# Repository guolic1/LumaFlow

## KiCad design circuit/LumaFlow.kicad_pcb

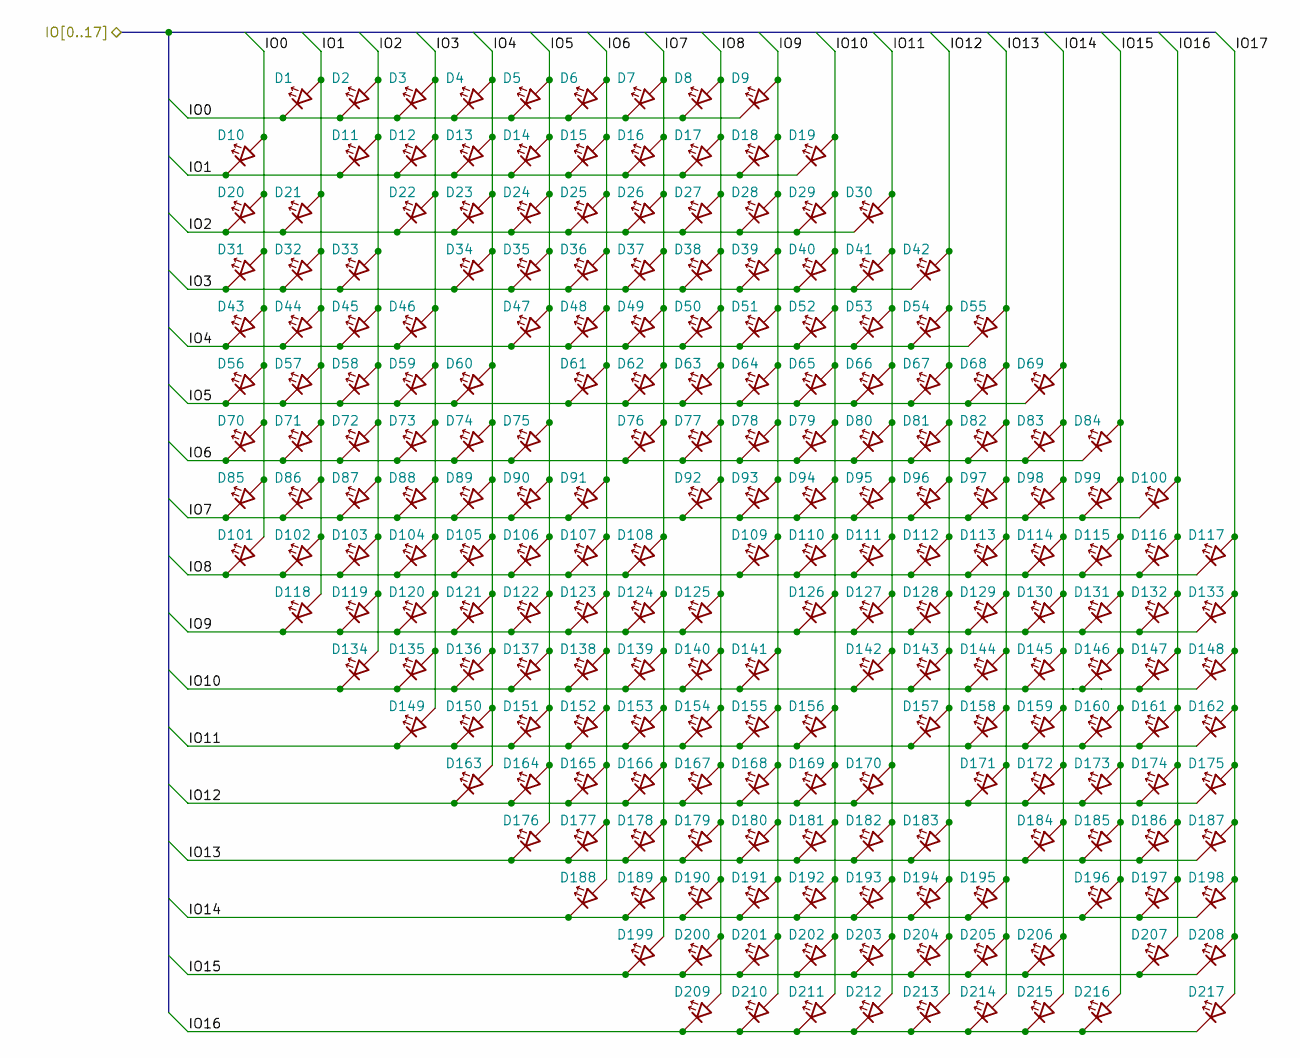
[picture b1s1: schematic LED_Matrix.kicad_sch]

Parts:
D1, D2, D3, D4, D5, D6, D7, D8, D9, D10, D11, D12, D13, D14, D15, D16, D17, D18, D19, D20, D21, D22, D23, D24, D25, D26, D27, D28, D29, D30, D31, D32, D33, D34, D35, D36, D37, D38, D39, D40, D41, D42, D43, D44, D45, D46, D47, D48, D49, D50, D51, D52, D53, D54, D55, D56, D57, D58, D59, D60, D61, D62, D63, D64, D65, D66, D67, D68, D69, D70, D71, D72, D73, D74, D75, D76, D77, D78, D79, D80, D81, D82, D83, D84, D85, D86, D87, D88, D89, D90, D91, D92, D93, D94, D95, D96, D97, D98, D99, D100, D101, D102, D103, D104, D105, D106, D107, D108, D109, D110, D111, D112, D113, D114, D115, D116, D117, D118, D119, D120, D121, D122, D123, D124, D125, D126, D127, D128, D129, D130, D131, D132, D133, D134, D135, D136, D137, D138, D139, D140, D141, D142, D143, D144, D145, D146, D147, D148, D149, D150, D151, D152, D153, D154, D155, D156, D157, D158, D159, D160, D161, D162, D163, D164, D165, D166, D167, D168, D169, D170, D171, D172, D173, D174, D175, D176, D177, D178, D179, D180, D181, D182, D183, D184, D185, D186, D187, D188, D189, D190, D191, D192, D193, D194, D195, D196, D197, D198, D199, D200, D201, D202, D203, D204, D205, D206, D207, D208, D209, D210, D211, D212, D213, D214, D215, D216, D217: LED; LED_0402_1005Metric

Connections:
/LED Matrix/IO0: D1.1 (K), D2.1 (K), D3.1 (K), D4.1 (K), D5.1 (K), D6.1 (K), D7.1 (K), D8.1 (K), D9.1 (K), D10.2 (A), D20.2 (A), D31.2 (A), D43.2 (A), D56.2 (A), D70.2 (A), D85.2 (A), D101.2 (A); also elsewhere on the board
/LED Matrix/IO1: D1.2 (A), D10.1 (K), D11.1 (K), D12.1 (K), D13.1 (K), D14.1 (K), D15.1 (K), D16.1 (K), D17.1 (K), D18.1 (K), D19.1 (K), D21.2 (A), D32.2 (A), D44.2 (A), D57.2 (A), D71.2 (A), D86.2 (A), D102.2 (A), D118.2 (A); also elsewhere on the board
/LED Matrix/IO2: D2.2 (A), D11.2 (A), D20.1 (K), D21.1 (K), D22.1 (K), D23.1 (K), D24.1 (K), D25.1 (K), D26.1 (K), D27.1 (K), D28.1 (K), D29.1 (K), D30.1 (K), D33.2 (A), D45.2 (A), D58.2 (A), D72.2 (A), D87.2 (A), D103.2 (A), D119.2 (A), D134.2 (A); also elsewhere on the board
/LED Matrix/IO3: D3.2 (A), D12.2 (A), D22.2 (A), D31.1 (K), D32.1 (K), D33.1 (K), D34.1 (K), D35.1 (K), D36.1 (K), D37.1 (K), D38.1 (K), D39.1 (K), D40.1 (K), D41.1 (K), D42.1 (K), D46.2 (A), D59.2 (A), D73.2 (A), D88.2 (A), D104.2 (A), D120.2 (A), D135.2 (A), D149.2 (A); also elsewhere on the board
/LED Matrix/IO4: D4.2 (A), D13.2 (A), D23.2 (A), D34.2 (A), D43.1 (K), D44.1 (K), D45.1 (K), D46.1 (K), D47.1 (K), D48.1 (K), D49.1 (K), D50.1 (K), D51.1 (K), D52.1 (K), D53.1 (K), D54.1 (K), D55.1 (K), D60.2 (A), D74.2 (A), D89.2 (A), D105.2 (A), D121.2 (A), D136.2 (A), D150.2 (A), D163.2 (A); also elsewhere on the board
/LED Matrix/IO5: D5.2 (A), D14.2 (A), D24.2 (A), D35.2 (A), D47.2 (A), D56.1 (K), D57.1 (K), D58.1 (K), D59.1 (K), D60.1 (K), D61.1 (K), D62.1 (K), D63.1 (K), D64.1 (K), D65.1 (K), D66.1 (K), D67.1 (K), D68.1 (K), D69.1 (K), D75.2 (A), D90.2 (A), D106.2 (A), D122.2 (A), D137.2 (A), D151.2 (A), D164.2 (A), D176.2 (A); also elsewhere on the board
/LED Matrix/IO6: D6.2 (A), D15.2 (A), D25.2 (A), D36.2 (A), D48.2 (A), D61.2 (A), D70.1 (K), D71.1 (K), D72.1 (K), D73.1 (K), D74.1 (K), D75.1 (K), D76.1 (K), D77.1 (K), D78.1 (K), D79.1 (K), D80.1 (K), D81.1 (K), D82.1 (K), D83.1 (K), D84.1 (K), D91.2 (A), D107.2 (A), D123.2 (A), D138.2 (A), D152.2 (A), D165.2 (A), D177.2 (A), D188.2 (A); also elsewhere on the board
/LED Matrix/IO7: D7.2 (A), D16.2 (A), D26.2 (A), D37.2 (A), D49.2 (A), D62.2 (A), D76.2 (A), D85.1 (K), D86.1 (K), D87.1 (K), D88.1 (K), D89.1 (K), D90.1 (K), D91.1 (K), D92.1 (K), D93.1 (K), D94.1 (K), D95.1 (K), D96.1 (K), D97.1 (K), D98.1 (K), D99.1 (K), D100.1 (K), D108.2 (A), D124.2 (A), D139.2 (A), D153.2 (A), D166.2 (A), D178.2 (A), D189.2 (A), D199.2 (A); also elsewhere on the board
/LED Matrix/IO8: D8.2 (A), D17.2 (A), D27.2 (A), D38.2 (A), D50.2 (A), D63.2 (A), D77.2 (A), D92.2 (A), D101.1 (K), D102.1 (K), D103.1 (K), D104.1 (K), D105.1 (K), D106.1 (K), D107.1 (K), D108.1 (K), D109.1 (K), D110.1 (K), D111.1 (K), D112.1 (K), D113.1 (K), D114.1 (K), D115.1 (K), D116.1 (K), D117.1 (K), D125.2 (A), D140.2 (A), D154.2 (A), D167.2 (A), D179.2 (A), D190.2 (A), D200.2 (A), D209.2 (A); also elsewhere on the board
/LED Matrix/IO9: D9.2 (A), D18.2 (A), D28.2 (A), D39.2 (A), D51.2 (A), D64.2 (A), D78.2 (A), D93.2 (A), D109.2 (A), D118.1 (K), D119.1 (K), D120.1 (K), D121.1 (K), D122.1 (K), D123.1 (K), D124.1 (K), D125.1 (K), D126.1 (K), D127.1 (K), D128.1 (K), D129.1 (K), D130.1 (K), D131.1 (K), D132.1 (K), D133.1 (K), D141.2 (A), D155.2 (A), D168.2 (A), D180.2 (A), D191.2 (A), D201.2 (A), D210.2 (A); also elsewhere on the board
/LED Matrix/IO10: D19.2 (A), D29.2 (A), D40.2 (A), D52.2 (A), D65.2 (A), D79.2 (A), D94.2 (A), D110.2 (A), D126.2 (A), D134.1 (K), D135.1 (K), D136.1 (K), D137.1 (K), D138.1 (K), D139.1 (K), D140.1 (K), D141.1 (K), D142.1 (K), D143.1 (K), D144.1 (K), D145.1 (K), D146.1 (K), D147.1 (K), D148.1 (K), D156.2 (A), D169.2 (A), D181.2 (A), D192.2 (A), D202.2 (A), D211.2 (A); also elsewhere on the board
/LED Matrix/IO11: D30.2 (A), D41.2 (A), D53.2 (A), D66.2 (A), D80.2 (A), D95.2 (A), D111.2 (A), D127.2 (A), D142.2 (A), D149.1 (K), D150.1 (K), D151.1 (K), D152.1 (K), D153.1 (K), D154.1 (K), D155.1 (K), D156.1 (K), D157.1 (K), D158.1 (K), D159.1 (K), D160.1 (K), D161.1 (K), D162.1 (K), D170.2 (A), D182.2 (A), D193.2 (A), D203.2 (A), D212.2 (A); also elsewhere on the board
/LED Matrix/IO12: D42.2 (A), D54.2 (A), D67.2 (A), D81.2 (A), D96.2 (A), D112.2 (A), D128.2 (A), D143.2 (A), D157.2 (A), D163.1 (K), D164.1 (K), D165.1 (K), D166.1 (K), D167.1 (K), D168.1 (K), D169.1 (K), D170.1 (K), D171.1 (K), D172.1 (K), D173.1 (K), D174.1 (K), D175.1 (K), D183.2 (A), D194.2 (A), D204.2 (A), D213.2 (A); also elsewhere on the board
/LED Matrix/IO13: D55.2 (A), D68.2 (A), D82.2 (A), D97.2 (A), D113.2 (A), D129.2 (A), D144.2 (A), D158.2 (A), D171.2 (A), D176.1 (K), D177.1 (K), D178.1 (K), D179.1 (K), D180.1 (K), D181.1 (K), D182.1 (K), D183.1 (K), D184.1 (K), D185.1 (K), D186.1 (K), D187.1 (K), D195.2 (A), D205.2 (A), D214.2 (A); also elsewhere on the board
/LED Matrix/IO14: D69.2 (A), D83.2 (A), D98.2 (A), D114.2 (A), D130.2 (A), D145.2 (A), D159.2 (A), D172.2 (A), D184.2 (A), D188.1 (K), D189.1 (K), D190.1 (K), D191.1 (K), D192.1 (K), D193.1 (K), D194.1 (K), D195.1 (K), D196.1 (K), D197.1 (K), D198.1 (K), D206.2 (A), D215.2 (A); also elsewhere on the board
/LED Matrix/IO15: D84.2 (A), D99.2 (A), D115.2 (A), D131.2 (A), D146.2 (A), D160.2 (A), D173.2 (A), D185.2 (A), D196.2 (A), D199.1 (K), D200.1 (K), D201.1 (K), D202.1 (K), D203.1 (K), D204.1 (K), D205.1 (K), D206.1 (K), D207.1 (K), D208.1 (K), D216.2 (A); also elsewhere on the board
/LED Matrix/IO16: D100.2 (A), D116.2 (A), D132.2 (A), D147.2 (A), D161.2 (A), D174.2 (A), D186.2 (A), D197.2 (A), D207.2 (A), D209.1 (K), D210.1 (K), D211.1 (K), D212.1 (K), D213.1 (K), D214.1 (K), D215.1 (K), D216.1 (K), D217.1 (K); also elsewhere on the board
/LED Matrix/IO17: D117.2 (A), D133.2 (A), D148.2 (A), D162.2 (A), D175.2 (A), D187.2 (A), D198.2 (A), D208.2 (A), D217.2 (A); also elsewhere on the board

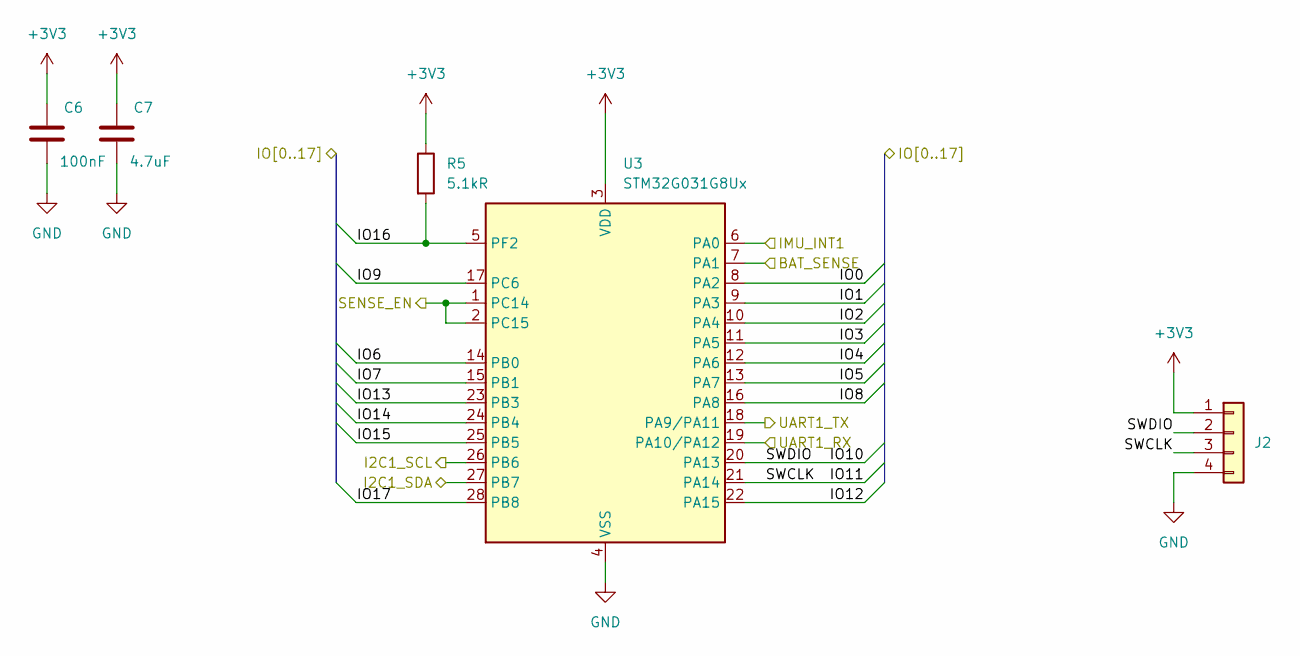
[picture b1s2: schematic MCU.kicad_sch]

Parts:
C6: 100nF; C_0402_1005Metric
C7: 4.7uF; C_0402_1005Metric
J2: Conn_01x04; PinSocket_1x04_P1.27mm_Vertical
R5: 5.1kR; R_0402_1005Metric
U3: STM32G031G8Ux; QFN-28_4x4mm_P0.5mm

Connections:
+3V3: C6.1, C7.1, J2.1, R5.1, U3.3 (VDD); also elsewhere on the board
/IMU/INT1: U3.6 (PA0); also elsewhere on the board
/IMU/SCL: U3.26 (PB6); also elsewhere on the board
/IMU/SDA: U3.27 (PB7); also elsewhere on the board
/LED Matrix/IO0: U3.8 (PA2); also elsewhere on the board
/LED Matrix/IO1: U3.9 (PA3); also elsewhere on the board
/LED Matrix/IO2: U3.10 (PA4); also elsewhere on the board
/LED Matrix/IO3: U3.11 (PA5); also elsewhere on the board
/LED Matrix/IO4: U3.12 (PA6); also elsewhere on the board
/LED Matrix/IO5: U3.13 (PA7); also elsewhere on the board
/LED Matrix/IO6: U3.14 (PB0); also elsewhere on the board
/LED Matrix/IO7: U3.15 (PB1); also elsewhere on the board
/LED Matrix/IO8: U3.16 (PA8); also elsewhere on the board
/LED Matrix/IO9: U3.17 (PC6); also elsewhere on the board
/LED Matrix/IO10: J2.2, U3.20 (PA13); also elsewhere on the board
/LED Matrix/IO11: J2.3, U3.21 (PA14); also elsewhere on the board
/LED Matrix/IO12: U3.22 (PA15); also elsewhere on the board
/LED Matrix/IO13: U3.23 (PB3); also elsewhere on the board
/LED Matrix/IO14: U3.24 (PB4); also elsewhere on the board
/LED Matrix/IO15: U3.25 (PB5); also elsewhere on the board
/LED Matrix/IO16: R5.2, U3.5 (PF2); also elsewhere on the board
/LED Matrix/IO17: U3.28 (PB8); also elsewhere on the board
/MCU/BAT_SENSE: U3.7 (PA1); also elsewhere on the board
/MCU/SENSE_EN: U3.1 (PC14), U3.2 (PC15); also elsewhere on the board
/MCU/UART1_RX: U3.19 (PA10/PA12); also elsewhere on the board
/MCU/UART1_TX: U3.18 (PA9/PA11); also elsewhere on the board
GND: C6.2, C7.2, J2.4, U3.4 (VSS); also elsewhere on the board

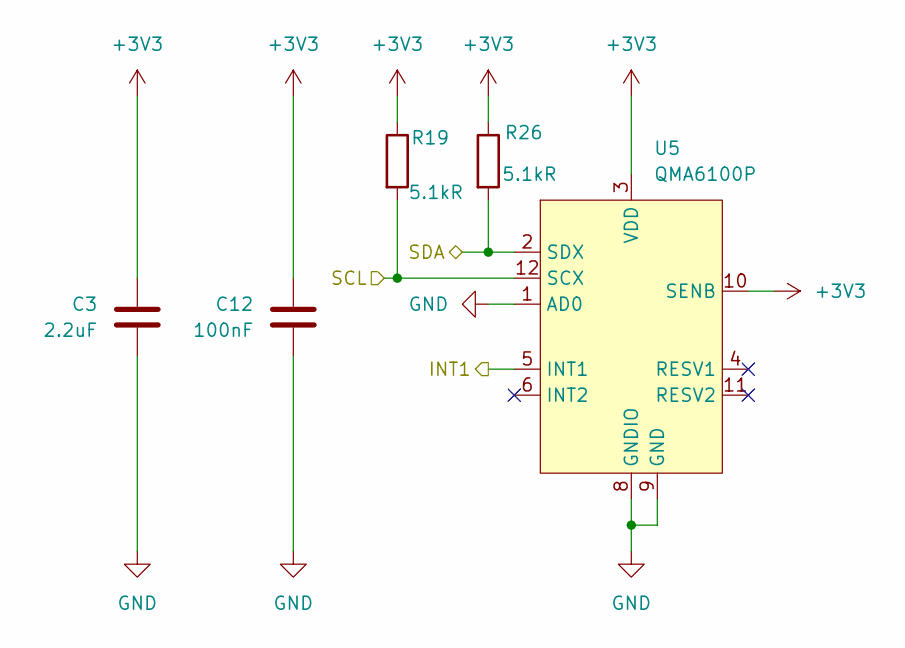
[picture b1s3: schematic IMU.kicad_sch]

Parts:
C3: 2.2uF; C_0402_1005Metric
C12: 100nF; C_0402_1005Metric
R19, R26: 5.1kR; R_0402_1005Metric
U5: QMA6100P; LGA-12_2x2mm_P0.5mm

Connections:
+3V3: C3.1, C12.1, R19.1, R26.1, U5.3 (VDD), U5.10 (SENB); also elsewhere on the board
/IMU/INT1: U5.5 (INT1); also elsewhere on the board
/IMU/SCL: R19.2, U5.12 (SCX); also elsewhere on the board
/IMU/SDA: R26.2, U5.2 (SDX); also elsewhere on the board
GND: C3.2, C12.2, U5.1 (AD0), U5.8 (GNDIO), U5.9 (GND); also elsewhere on the board

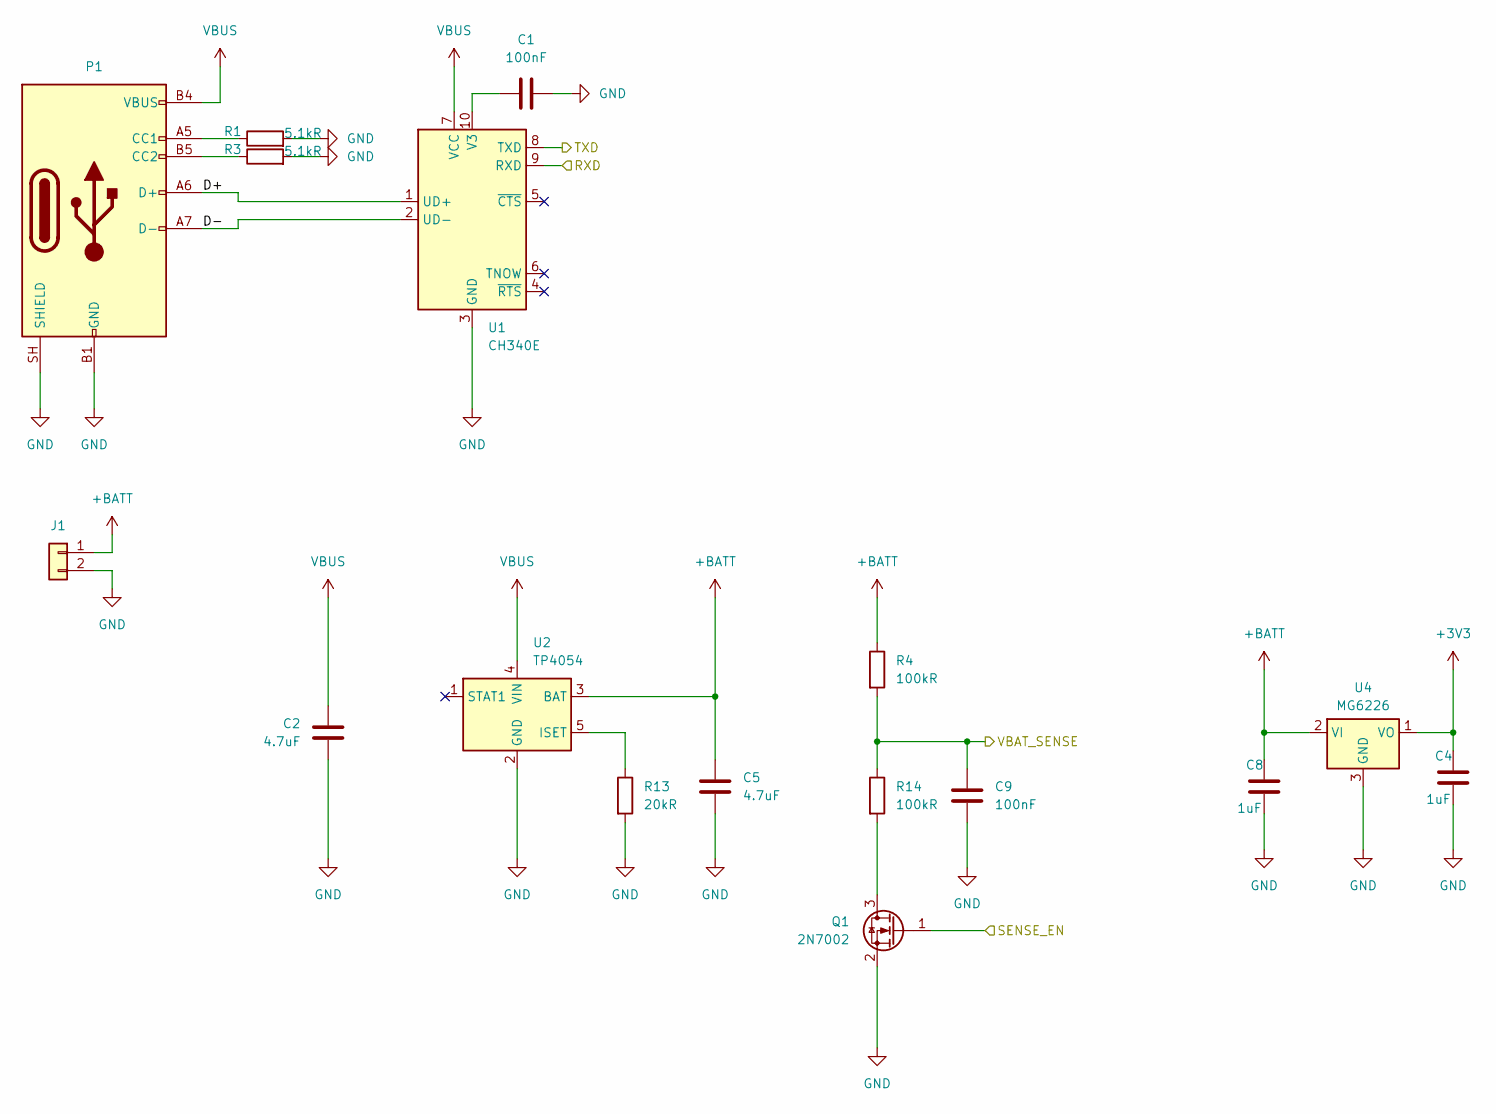
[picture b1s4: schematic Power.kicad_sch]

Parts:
C1, C9: 100nF; C_0402_1005Metric
C2, C5: 4.7uF; C_0402_1005Metric
C4, C8: 1uF; C_0402_1005Metric
J1: Conn_01x02
P1: USB_C_Plug_USB2.0_8Pin; USB-C-SMD_MC-402L68
Q1: 2N7002; SOT-323_SC-70
R1, R3: 5.1kR; R_0402_1005Metric
R4, R14: 100kR; R_0402_1005Metric
R13: 20kR; R_0402_1005Metric
U1: CH340E; MSOP-10_3x3mm_P0.5mm
U2: TP4054; SOT-23-5
U4: MG6226; SOT-23-3

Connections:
+3V3: C4.1, U4.1 (VO); also elsewhere on the board
+BATT: C5.1, C8.1, J1.1, R4.1, U2.3 (BAT), U4.2 (VI)
/MCU/BAT_SENSE: C9.1, R4.2, R14.1; also elsewhere on the board
/MCU/SENSE_EN: Q1.1 (G); also elsewhere on the board
/MCU/UART1_RX: U1.8 (TXD); also elsewhere on the board
/MCU/UART1_TX: U1.9 (RXD); also elsewhere on the board
/Power/D+: P1.A6 (D+), U1.1 (UD+)
/Power/D-: P1.A7 (D-), U1.2 (UD-)
GND: C1.2, C2.2, C4.2, C5.2, C8.2, C9.2, J1.2, P1.B1 (GND), P1.B12 (GND), P1.SH (SHIELD), Q1.2 (S), R1.2, R3.2, R13.2, U1.3 (GND), U2.2 (GND), U4.3 (GND); also elsewhere on the board
unnamed: P1.A5 (CC1), R1.1
unnamed: P1.B5 (CC2), R3.1
unnamed: Q1.3 (D), R14.2
unnamed: C1.1, U1.10 (V3)
unnamed: R13.1, U2.5 (ISET)
VBUS: C2.1, P1.B4 (VBUS), P1.B9 (VBUS), U1.7 (VCC), U2.4 (VIN)

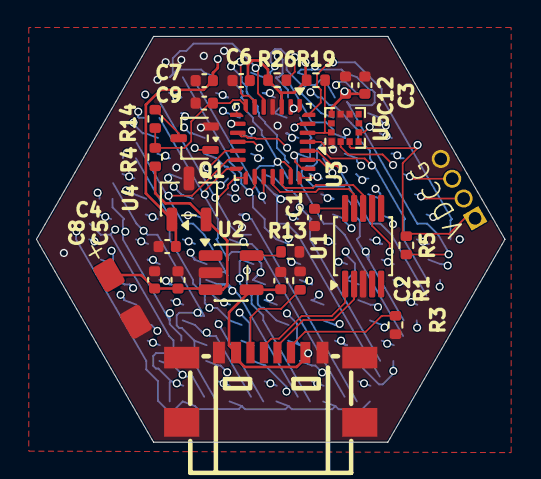
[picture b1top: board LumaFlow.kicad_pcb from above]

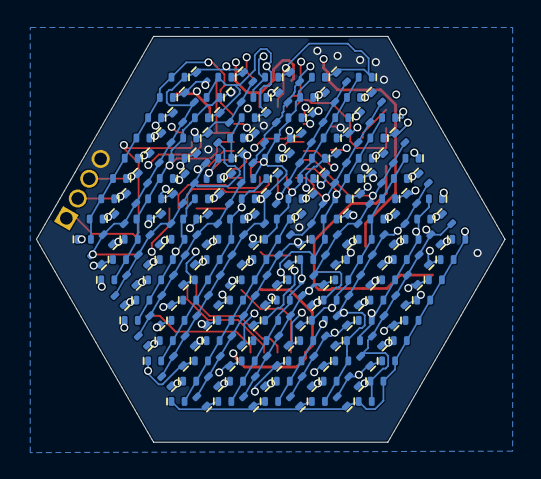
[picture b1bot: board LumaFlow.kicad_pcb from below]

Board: 4 copper layers, 26.0 x 22.5 mm, 244 parts (217 on the bottom side), 36 nets.

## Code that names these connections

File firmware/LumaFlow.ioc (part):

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Mcu.Name=STM32G031G(4-6-8)Ux
Mcu.Package=UFQFPN28
Mcu.UserName=STM32G031G8Ux
PA0.GPIOParameters=GPIO_Label
PA0.GPIO_Label=IMU_INT
PA0.Signal=GPXTI0
PA1.GPIOParameters=GPIO_Label
PA1.GPIO_Label=BAT_SENSE
PA1.Mode=IN1
PA1.Signal=ADC1_IN1
PA10\ [PA12].Mode=Asynchronous
PA10\ [PA12].Signal=USART1_RX
PA13.GPIOParameters=GPIO_Label
PA13.GPIO_Label=IO10
PA13.Mode=Serial_Wire
PA13.Signal=SYS_SWDIO
PA14-BOOT0.GPIOParameters=GPIO_Label
PA14-BOOT0.GPIO_Label=IO11
PA14-BOOT0.Mode=Serial_Wire
PA14-BOOT0.Signal=SYS_SWCLK
PA15.GPIOParameters=GPIO_Speed,GPIO_Label
PA15.GPIO_Label=IO12
PA15.GPIO_Speed=GPIO_SPEED_FREQ_HIGH
PA15.Signal=GPIO_Output
PA2.GPIOParameters=GPIO_Speed,GPIO_Label
PA2.GPIO_Label=IO0
PA2.GPIO_Speed=GPIO_SPEED_FREQ_HIGH
PA2.Signal=GPIO_Output
PA3.GPIOParameters=GPIO_Speed,GPIO_Label
PA3.GPIO_Label=IO1
PA3.GPIO_Speed=GPIO_SPEED_FREQ_HIGH
PA3.Signal=GPIO_Output
PA4.GPIOParameters=GPIO_Speed,GPIO_Label
PA4.GPIO_Label=IO2
PA4.GPIO_Speed=GPIO_SPEED_FREQ_HIGH
PA4.Signal=GPIO_Output
PA5.GPIOParameters=GPIO_Speed,GPIO_Label
PA5.GPIO_Label=IO3
PA5.GPIO_Speed=GPIO_SPEED_FREQ_HIGH
PA5.Signal=GPIO_Output
PA6.GPIOParameters=GPIO_Speed,GPIO_Label
PA6.GPIO_Label=IO4
PA6.GPIO_Speed=GPIO_SPEED_FREQ_HIGH
PA6.Signal=GPIO_Output
PA7.GPIOParameters=GPIO_Speed,GPIO_Label
PA7.GPIO_Label=IO5
PA7.GPIO_Speed=GPIO_SPEED_FREQ_HIGH
PA7.Signal=GPIO_Output
PA8.GPIOParameters=GPIO_Speed,GPIO_Label
PA8.GPIO_Label=IO8
PA8.GPIO_Speed=GPIO_SPEED_FREQ_HIGH
PA8.Signal=GPIO_Output
PA9\ [PA11].Mode=Asynchronous
PA9\ [PA11].Signal=USART1_TX
PB0.GPIOParameters=GPIO_Speed,GPIO_Label
PB0.GPIO_Label=IO6
PB0.GPIO_Speed=GPIO_SPEED_FREQ_HIGH
PB0.Signal=GPIO_Output
PB1.GPIOParameters=GPIO_Speed,GPIO_Label
PB1.GPIO_Label=IO7
PB1.GPIO_Speed=GPIO_SPEED_FREQ_HIGH
PB1.Signal=GPIO_Output
PB3.GPIOParameters=GPIO_Speed,GPIO_Label
PB3.GPIO_Label=IO13
PB3.GPIO_Speed=GPIO_SPEED_FREQ_HIGH
PB3.Signal=GPIO_Output
PB4.GPIOParameters=GPIO_Speed,GPIO_Label
PB4.GPIO_Label=IO14
PB4.GPIO_Speed=GPIO_SPEED_FREQ_HIGH
PB4.Signal=GPIO_Output
PB5.GPIOParameters=GPIO_Speed,GPIO_Label
PB5.GPIO_Label=IO15
PB5.GPIO_Speed=GPIO_SPEED_FREQ_HIGH
PB5.Signal=GPIO_Output
PB6.Mode=I2C
PB6.Signal=I2C1_SCL
PB7.Mode=I2C
PB7.Signal=I2C1_SDA
PB8.GPIOParameters=GPIO_Speed,GPIO_Label
PB8.GPIO_Label=IO17
PB8.GPIO_Speed=GPIO_SPEED_FREQ_HIGH
PB8.Signal=GPIO_Output
PC14-OSC32_IN\ (PC14).GPIOParameters=GPIO_PuPd,GPIO_Label
PC14-OSC32_IN\ (PC14).GPIO_Label=SENSE_EN
PC14-OSC32_IN\ (PC14).GPIO_PuPd=GPIO_PULLDOWN
PC14-OSC32_IN\ (PC14).Signal=GPIO_Output
PC6.GPIOParameters=GPIO_Speed,GPIO_Label
PC6.GPIO_Label=IO9
PC6.GPIO_Speed=GPIO_SPEED_FREQ_HIGH
PC6.Signal=GPIO_Output
PF2\ -\ NRST.GPIOParameters=GPIO_Speed,GPIO_Label
PF2\ -\ NRST.GPIO_Label=IO16
PF2\ -\ NRST.GPIO_Speed=GPIO_SPEED_FREQ_HIGH
PF2\ -\ NRST.Signal=GPIO_Output
RCC.HSE_VALUE=8000000
RCC.SYSCLKFreq_VALUE=64000000
RCC.SYSCLKSource=RCC_SYSCLKSOURCE_PLLCLK
board=custom
